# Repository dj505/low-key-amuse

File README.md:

# low-key-amuse
A low-key e-amusement keypad for DDR cabs (and other cabs? :eyes:)  
  
(Dimensions may vary with revisions!)

# Bill of Materials
|           Part           | Qty |              Description              |
|--------------------------|-----|---------------------------------------|
|MPR121                    |1    |Touch sensor                           |
|16 pin FFC                |1    |Reverse direction, 1mm pitch           |
|100nF capacitor           |2    |SMD, 0805 package                      |
|75k ohm resistor          |1    |SMD, 0805 package                      |
|4.2k ohm resistor         |2    |SMD, 0805 package                      |
|Raspberry Pi Pico         |1    |                                       |
|TE Connectivity 1-84952-6 |2    |FPC connector, 16 pin, bottom contacts |

**Notes:**
* Be sure the ribbon cables you purchase match the connectors. "Forward" direction ribbons will require you to use connectors with top contacts, however I would recommend "reverse" direction ribbons with bottom contact connectors.
* Some PCBA services might not carry 4.2k ohm resistors, or they may be difficult to find. Anything from 2k to 10k ohms should work. This is just what worked for me personally in testing.

# Required Libraries
All of the required libraries can be found in the [library bundle] for your installed version of CircuitPython. This project was built and tested with 8.x.x. The following should be placed in the `lib` folder on the `CIRCUITPY` drive:
* adafruit_bus_device
* adafruit_hid
* adafruit_mpr121.mpy

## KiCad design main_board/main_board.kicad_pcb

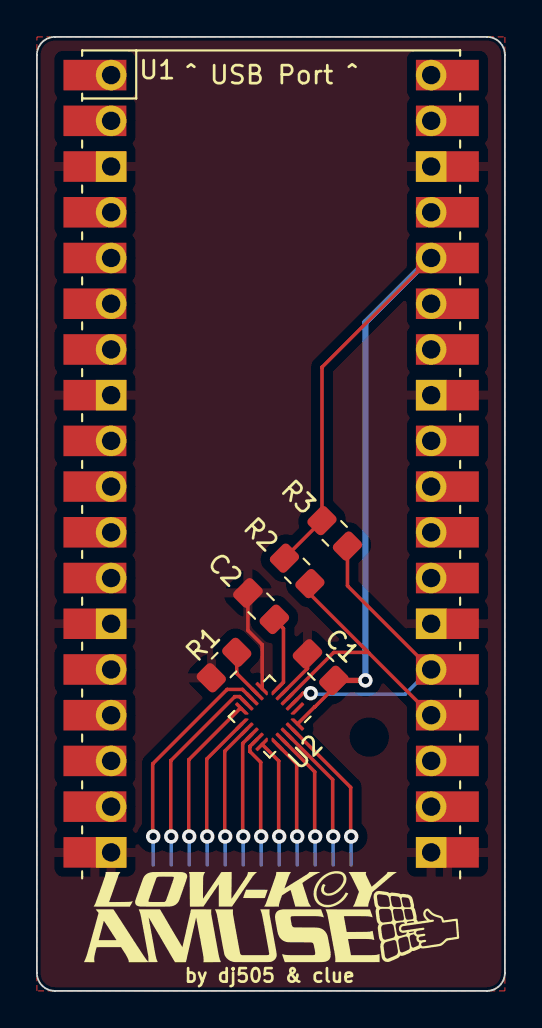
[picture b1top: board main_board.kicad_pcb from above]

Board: 2 copper layers, 26.0 x 53.0 mm, 8 parts (1 on the bottom side), 18 nets.

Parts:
C1, C2: 100nF; C_0805_2012Metric_Pad1.18x1.45mm_HandSolder
J1: Conn_01x16; TE_1-84952-6_1x16-1MP_P1.0mm_Horizontal
R1: 75k; R_0805_2012Metric_Pad1.20x1.40mm_HandSolder
R2, R3: 4.2k; R_0805_2012Metric_Pad1.20x1.40mm_HandSolder
U1: Pico; RPi_Pico_SMD_TH
U2: MPR121QR2; UQFN-20_3x3mm_P0.4mm

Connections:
+3V3: C1.2, R2.2, R3.2, U1.36 (3V3), U2.20 (VDD)
GND: C1.1, C2.1, J1.1, J1.16, R1.1, U1.3 (GND), U1.8 (GND), U1.13 (GND), U1.18 (GND), U1.23 (GND), U1.28 (GND), U1.33 (AGND), U1.38 (GND), U2.4 (ADDR), U2.6 (VSS)
unnamed: R1.2, U2.7 (REXT)
unnamed: C2.2, U2.5 (VREG)
PAD0: J1.15, U2.8 (ELE0)
PAD1: J1.14, U2.9 (ELE1)
PAD2: J1.13, U2.10 (ELE2)
PAD3: J1.12, U2.11 (ELE3)
PAD4: J1.11, U2.12 (LED0/ELE4)
PAD5: J1.10, U2.13 (LED1/ELE5)
PAD6: J1.9, U2.14 (LED2/ELE6)
PAD7: J1.8, U2.15 (LED3/ELE7)
PAD8: J1.7, U2.16 (LED4/ELE8)
PAD9: J1.6, U2.17 (LED5/ELE9)
PAD10: J1.5, U2.18 (LED6/ELE10)
PAD11: J1.4, U2.19 (LED7/ELE11)
SCL: R3.1, U1.27 (GPIO21), U2.2 (SCL)
SDA: R2.1, U1.26 (GPIO20), U2.3 (SDA)

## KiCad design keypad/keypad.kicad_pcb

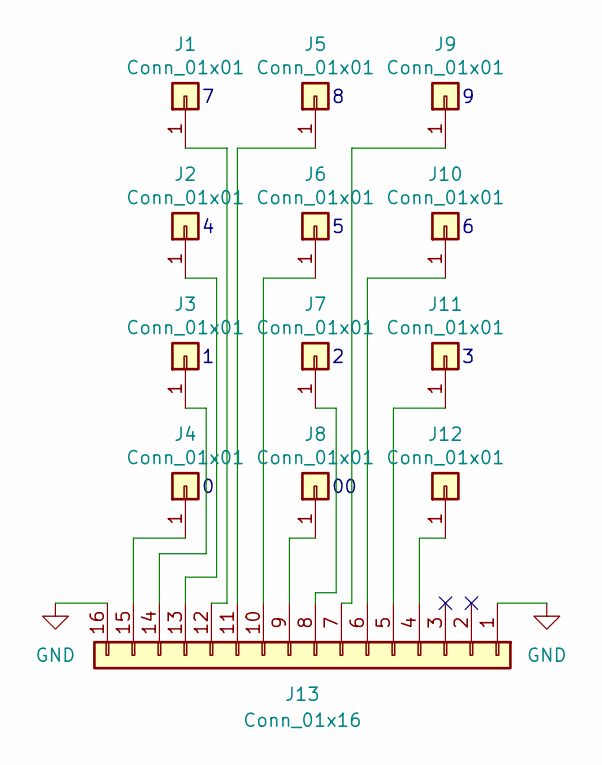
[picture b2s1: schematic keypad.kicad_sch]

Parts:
J1, J2, J3, J4, J5, J6, J7, J8, J9, J10, J11, J12: Conn_01x01
J13: Conn_01x16; TE_1-84952-6_1x16-1MP_P1.0mm_Horizontal

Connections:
GND: J13.1, J13.16
unnamed: J1.1, J13.12
unnamed: J10.1, J13.6
unnamed: J11.1, J13.5
unnamed: J12.1, J13.4
unnamed: J9.1, J13.7
unnamed: J7.1, J13.8
unnamed: J8.1, J13.9
unnamed: J6.1, J13.10
unnamed: J5.1, J13.11
unnamed: J2.1, J13.13
unnamed: J3.1, J13.14
unnamed: J4.1, J13.15

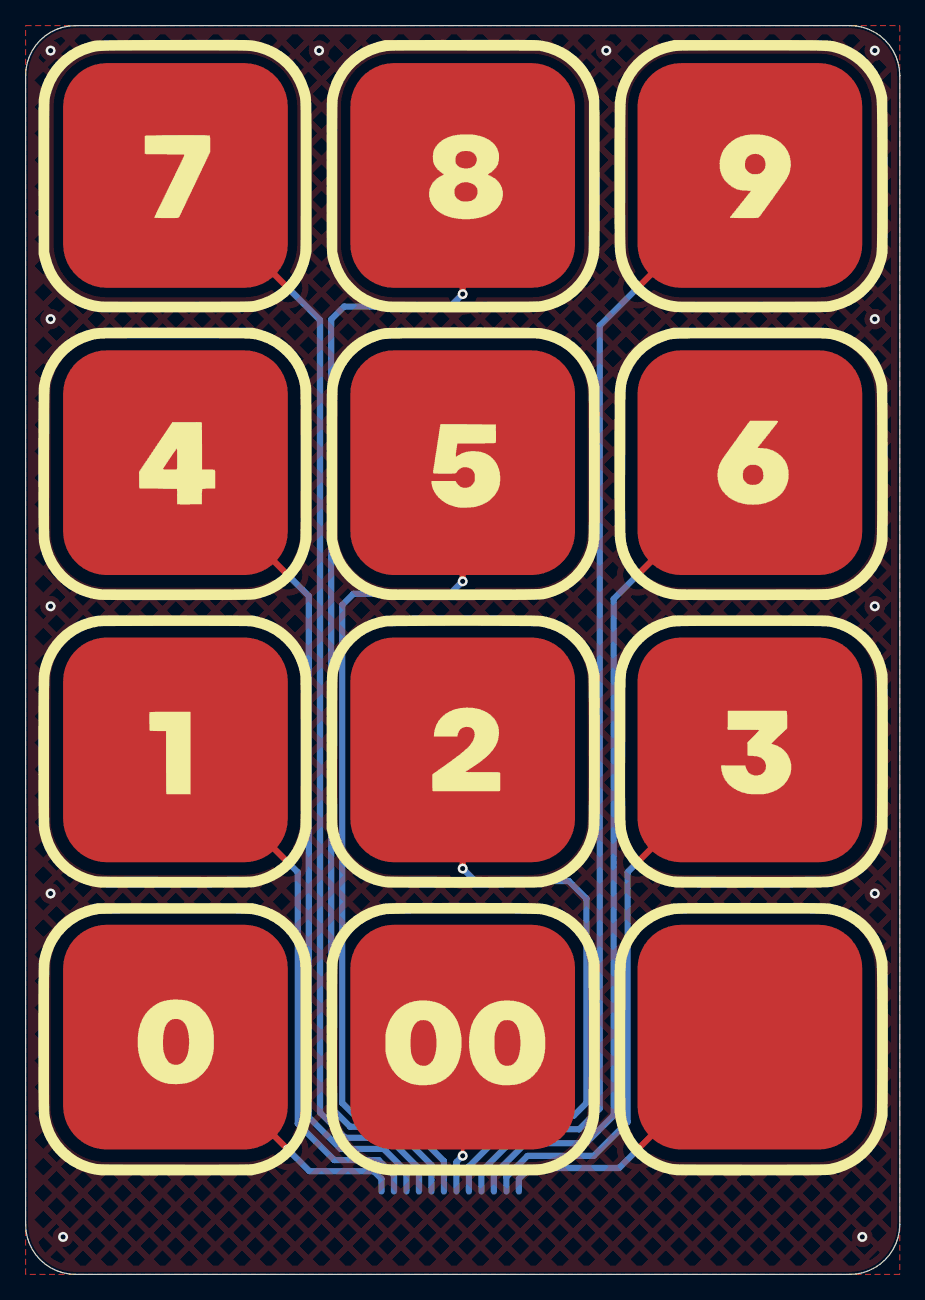
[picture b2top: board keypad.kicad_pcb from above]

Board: 2 copper layers, 70.0 x 100.0 mm, 13 parts (1 on the bottom side), 13 nets.

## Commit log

2023-02-16 First keypad design, initial footprints
2023-02-16 Create main board project, USB schematic
2023-02-17 Main board schematic updates
2023-02-17 done RP2040 routing, near final component layout
2023-03-01 keypad rev 1 done + gerber
2023-03-16 move to MPR121
2023-03-22 Main board complete?
2023-03-22 oops forgot to ctrl+S
2023-03-28 Alignment fixes, generate gerbers
2023-03-28 Add tooling holes, update logo, other adjustments
2023-03-28 didn't actually update gerbers last time oops
2023-03-28 Fic DRC errors
2023-03-28 remove sneaky REF*** text
2023-03-28 update files to match first prototype run
2023-04-17 Update keypad with ffc connector
2023-05-20 Add code.py, update gerbers/prod files
